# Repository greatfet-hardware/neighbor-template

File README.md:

# GreatFET Neighbor Template

KiCad templates for designing GreatFET neighbors

For usage instructions please read [How to Design a Neighbor](https://github.com/greatscottgadgets/greatfet/wiki/How-to-Design-a-Neighbor).

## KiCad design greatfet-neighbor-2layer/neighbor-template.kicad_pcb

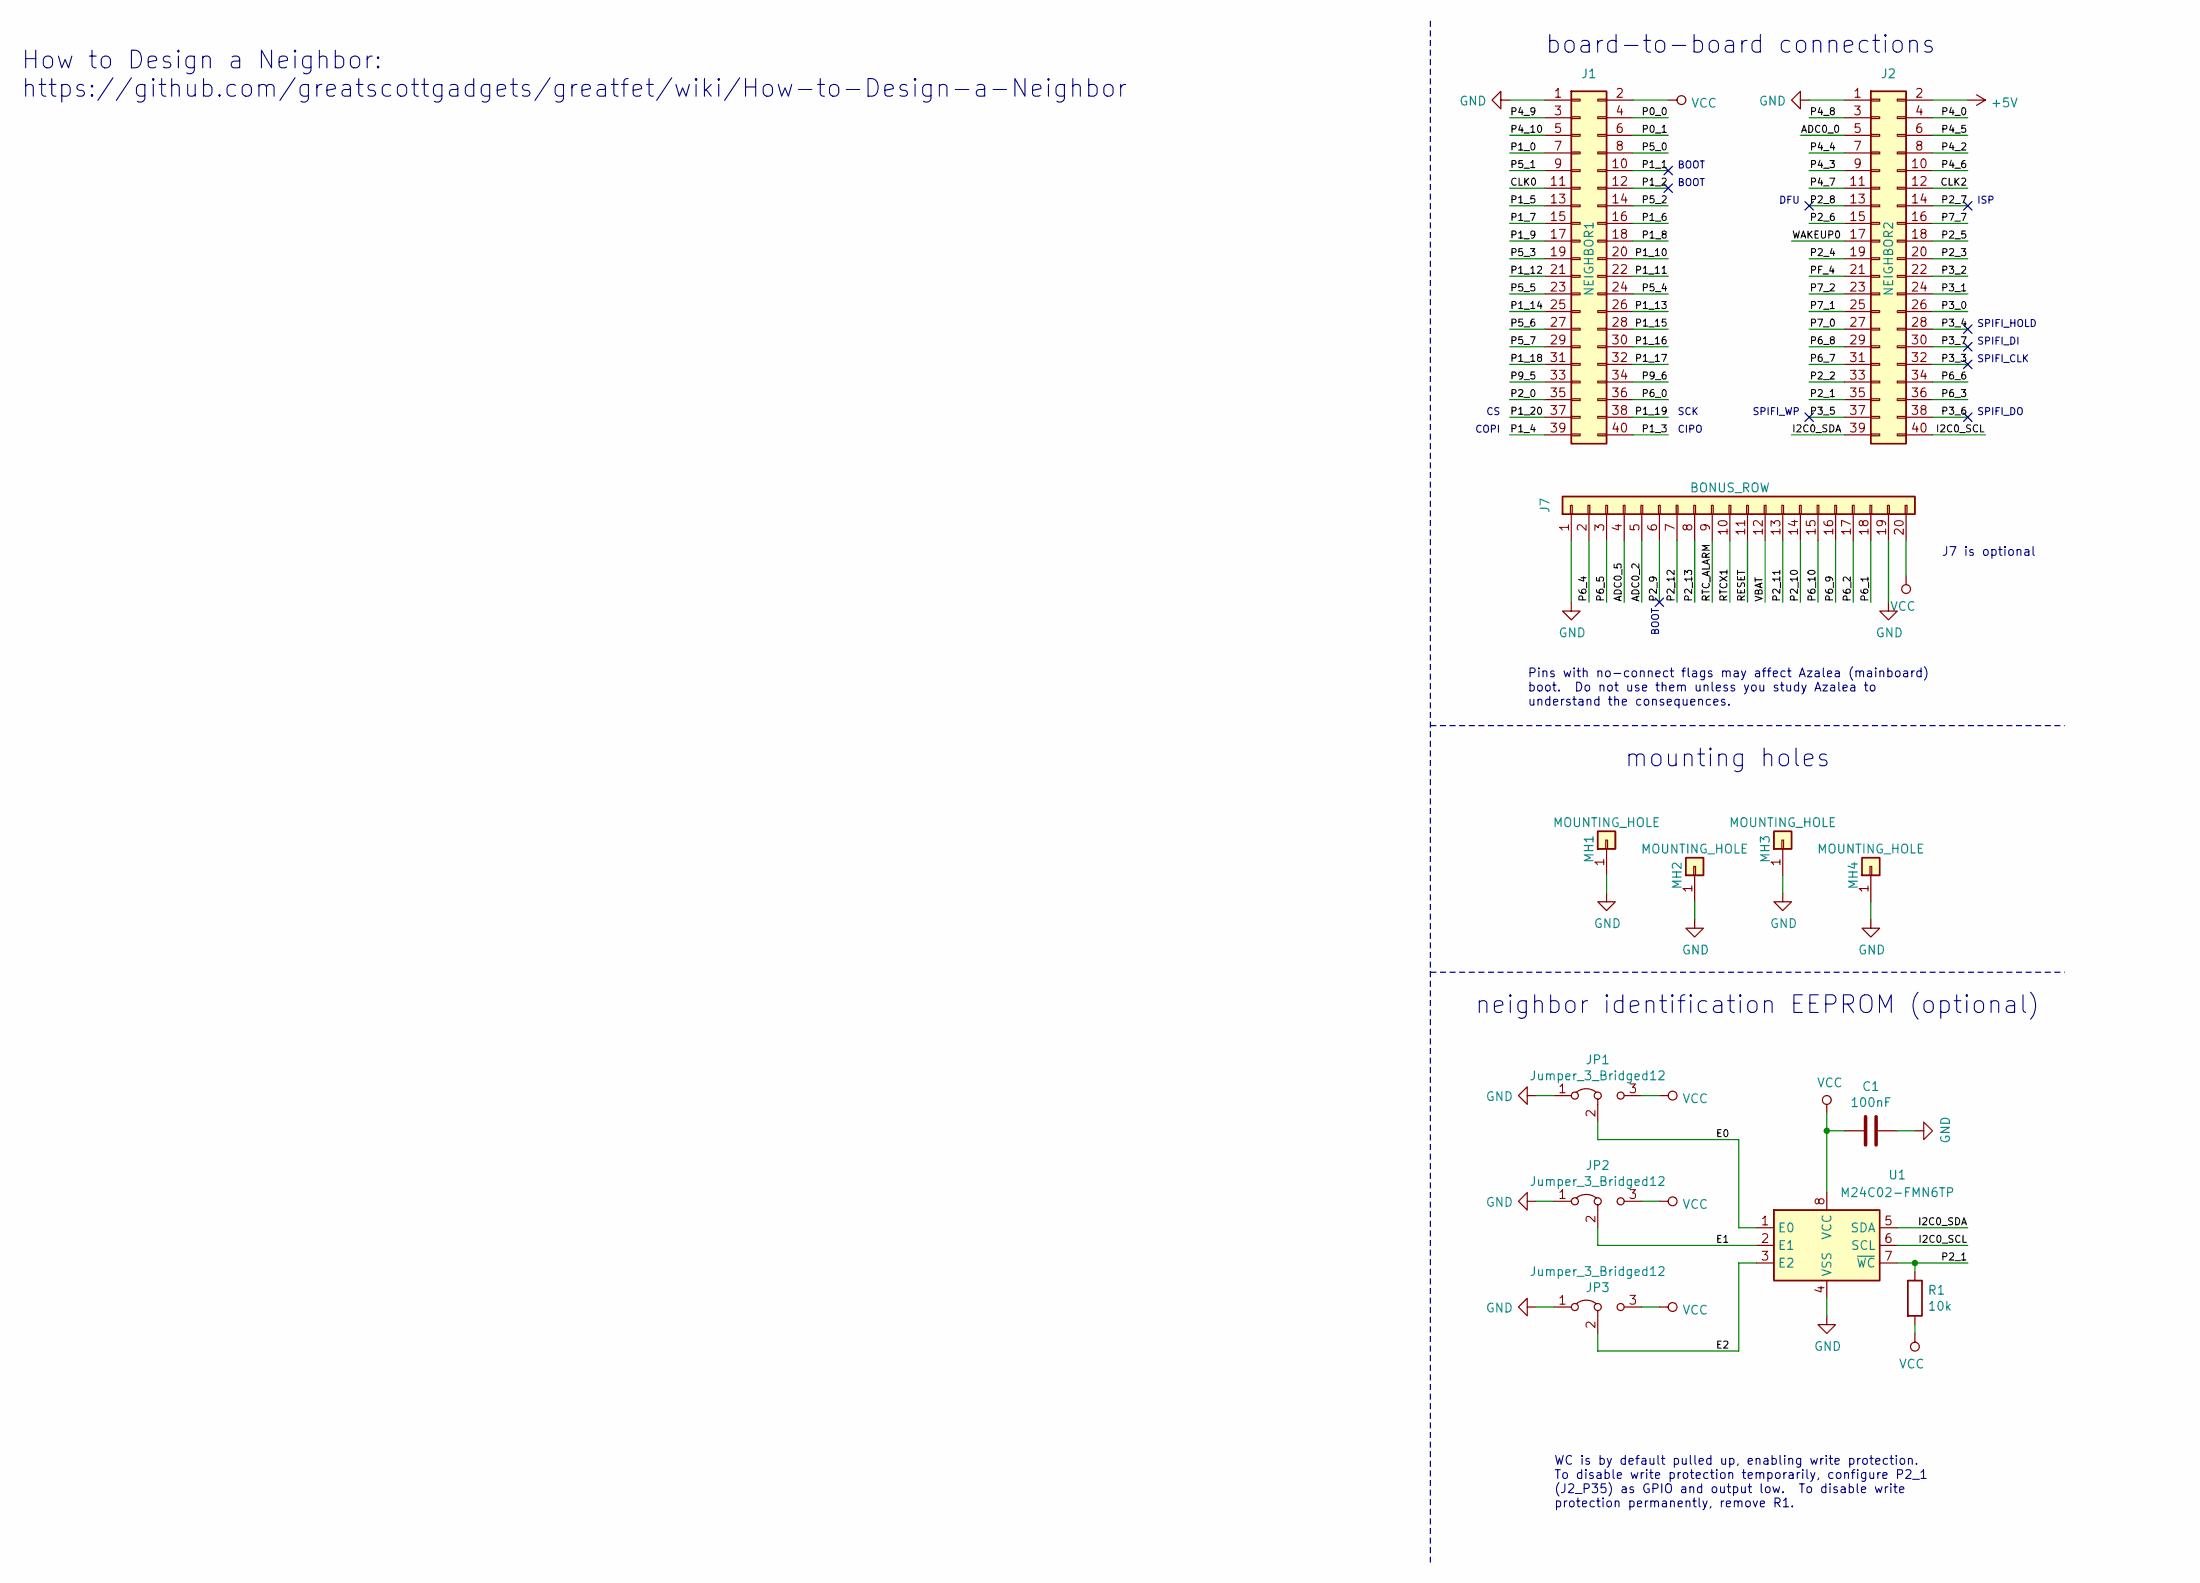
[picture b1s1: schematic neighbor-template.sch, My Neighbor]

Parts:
C1: 100nF; C_0603_1608Metric_Pad1.05x0.95mm_HandSolder
J1: NEIGHBOR1; HEADER-2x20; Part Number SSQ-120-23-G-D
J2: NEIGHBOR2; HEADER-2x20; Part Number SSQ-120-23-G-D
J7: BONUS_ROW; HEADER-1x20; Part Number SSQ-120-23-G-S
JP1, JP2, JP3: Jumper_3_Bridged12; 0603-JUMPER-3-BRIDGED12
MH1, MH2, MH3, MH4: MOUNTING_HOLE; HOLE126MIL-COPPER
R1: 10k; R_0603_1608Metric_Pad1.05x0.95mm_HandSolder
U1: M24C02-FMN6TP; SOIC-8_3.9x4.9mm_P1.27mm

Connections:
+5V: J2.2
/ADC0_0: J2.5
/ADC0_2: J7.5
/ADC0_5: J7.4
/CLK0: J1.11
/CLK2: J2.12
/E0: JP1.2 (C), U1.1 (E0)
/E1: JP2.2 (C), U1.2 (E1)
/E2: JP3.2 (C), U1.3 (E2)
/I2C0_SCL: J2.40, U1.6 (SCL)
/I2C0_SDA: J2.39, U1.5 (SDA)
/P0_0: J1.4
/P0_1: J1.6
/P1_0: J1.7
/P1_1: J1.10
/P1_2: J1.12
/P1_3: J1.40
/P1_4: J1.39
/P1_5: J1.13
/P1_6: J1.16
/P1_7: J1.15
/P1_8: J1.18
/P1_9: J1.17
/P1_10: J1.20
/P1_11: J1.22
/P1_12: J1.21
/P1_13: J1.26
/P1_14: J1.25
/P1_15: J1.28
/P1_16: J1.30
/P1_17: J1.32
/P1_18: J1.31
/P1_19: J1.38
/P1_20: J1.37
/P2_0: J1.35
/P2_1: J2.35, R1.1, U1.7 (~WC)
/P2_2: J2.33
/P2_3: J2.20
/P2_4: J2.19
/P2_5: J2.18
/P2_6: J2.15
/P2_7: J2.14
/P2_8: J2.13
/P2_9: J7.6
/P2_10: J7.14
/P2_11: J7.13
/P2_12: J7.7
/P2_13: J7.8
/P3_0: J2.26
/P3_1: J2.24
/P3_2: J2.22
/P3_3: J2.32
/P3_4: J2.28
/P3_5: J2.37
/P3_6: J2.38
/P3_7: J2.30
/P4_0: J2.4
/P4_2: J2.8
/P4_3: J2.9
/P4_4: J2.7
/P4_5: J2.6
/P4_6: J2.10
/P4_7: J2.11
/P4_8: J2.3
/P4_9: J1.3
/P4_10: J1.5
/P5_0: J1.8
/P5_1: J1.9
/P5_2: J1.14
/P5_3: J1.19
/P5_4: J1.24
/P5_5: J1.23
/P5_6: J1.27
/P5_7: J1.29
/P6_0: J1.36
/P6_1: J7.18
/P6_2: J7.17
/P6_3: J2.36
/P6_4: J7.2
/P6_5: J7.3
/P6_6: J2.34
/P6_7: J2.31
/P6_8: J2.29
/P6_9: J7.16
/P6_10: J7.15
/P7_0: J2.27
/P7_1: J2.25
/P7_2: J2.23
/P7_7: J2.16
/P9_5: J1.33
/P9_6: J1.34
/PF_4: J2.21
/RESET: J7.11
/RTCX1: J7.10
/RTC_ALARM: J7.9
/VBAT: J7.12
/WAKEUP0: J2.17
GND: C1.1, J1.1, J2.1, J7.1, J7.19, JP1.1 (A), JP2.1 (A), JP3.1 (A), MH1.1, MH2.1, MH3.1, MH4.1, U1.4 (VSS)
VCC: C1.2, J1.2, J7.20, JP1.3 (B), JP2.3 (B), JP3.3 (B), R1.2, U1.8 (VCC)

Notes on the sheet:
CIPO
COPI
SCK
ISP
DFU
BOOT
WC is by default pulled up, enabling write protection. To disable write protection temporarily, configure P2_1 (J2_P35) as GPIO and output low. To disable write protection permanently, remove R1.
SPIFI_CLK
SPIFI_HOLD
SPIFI_WP
SPIFI_DO
SPIFI_DI
Pins with no-connect flags may affect Azalea (mainboard) boot. Do not use them unless you study Azalea to understand the consequences.
board-to-board connections
mounting holes
J7 is optional
How to Design a Neighbor: https://github.com/greatscottgadgets/greatfet/wiki/How-to-Design-a-Neighbor
neighbor identification EEPROM (optional)

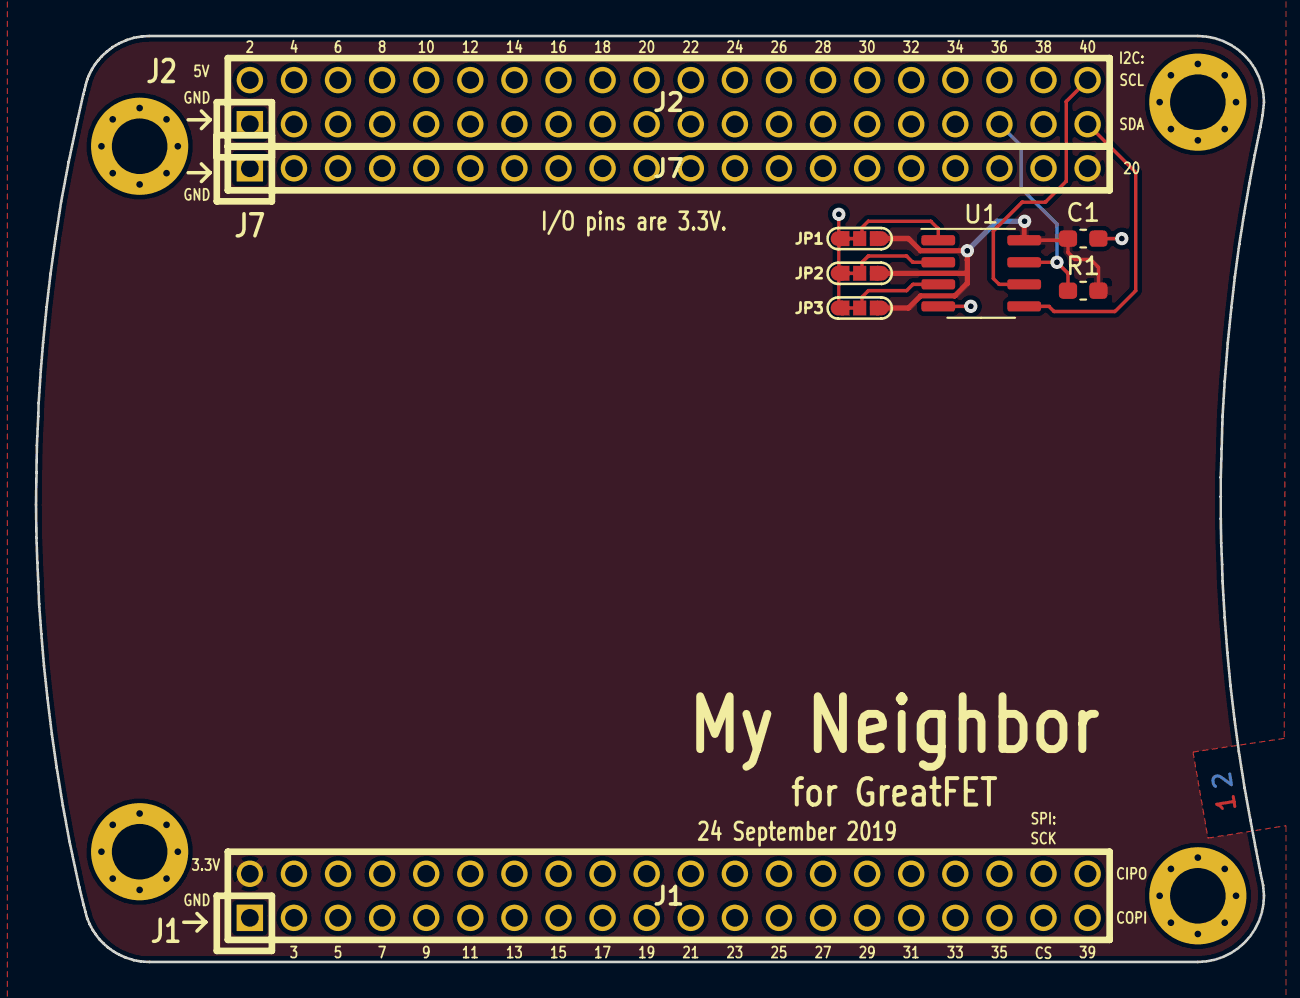
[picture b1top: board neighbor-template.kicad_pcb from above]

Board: 2 copper layers, 70.7 x 53.3 mm, 13 parts (0 on the bottom side), 8 nets.

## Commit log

2019-05-27 split neighbor-template into separate repository
2019-05-27 updated README.md to be neighbor-template-specific
2019-09-22 upate layout to KiCad 5.1 update .gitignore for KiCad 5.1 remove outdated library entries from *.pro
2019-09-22 add template meta files
2019-09-22 remove copyright and license from schematic so they are not imposed upon projects that copy this template update dates in schematic and layout
2019-09-22 copy gsg-kicad-lib footprints to local library remove gsg-kicad-lib dependency
2019-09-22 add local footprint library
2019-09-22 remove gsg-kicad-lib submodule
2019-09-23 change recommended alternate pin header parts fixes #1
2019-09-23 add links to How to Design a Neighbor closes #2
2019-09-23 add grid origin at center of PCB really at center of rectangle defined by J1 and J2 closes #3
2019-09-23 add no-connect flags to SPIFI and boot pins closes #4
2019-09-23 add identification EEPROM to layout
2019-09-23 remove Great Scott Gadgets branding
2019-09-23 change J7_P10 from GND to RTCX1 fixes #7
2019-09-23 change J2_P2 from VBUS to +5V fixes #8
2019-09-23 add pin numbers to silkscreen update silkscreen to match Azalea closes #5
2019-09-23 spruce up docs in meta directory
2019-09-25 move design to 4layer subfolder
2019-09-25 add 2layer template
2019-09-25 add "for GreatFET" to schematic, silkscreen add template README
2020-07-03 adopt OSHWA convention for SPI signal names https://www.oshwa.org/a-resolution-to-redefine-spi-signal-names
2021-01-14 label EEPROM_WC
2021-01-14 update license to CERN-OHL-P v2
